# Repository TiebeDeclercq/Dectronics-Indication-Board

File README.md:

# DECTRONICS INDICATION BOARD

The LED PCB is a versatile lighting interface board designed to connect standard LEDs and addressable WS2812B RGB LEDs to systems via FCP connectors or pin headers. It provides flexible soldering options to choose which connection option you want to use.
## Overview

This PCB serves as a lighting expansion board that can be integrated with various systems through standardized connectors. It features both power indicator LEDs and a chain of WS2812B addressable RGB LEDs, making it suitable for status indication, ambient lighting, and visual feedback in electronic projects.

## Features

- **Power/Status LEDs**: 4 individual LEDs with current-limiting resistors
- **WS2812B Support**: Chain of 6 addressable RGB LEDs
- **Dual FCP Connectors**: Front and back connection options
- **Header Connectors**: Standard 2.54mm pin headers for breadboard compatibility
- **Flexible Soldering**: Multiple connection points for different configurations
- **Mounting Holes**: Two mounting holes for secure installation
## Hardware Schematic

## Assembled PCB

## Connector Pinout
### FCP Connector (J2/J4)

| Pin | Function |
| --- | -------- |
| 1   | LED1/VCC |
| 2   | LED2     |
| 3   | LED3     |
| 4   | LED4     |
| 5   | LED5/RX  |
| 6   | LED6/TX  |
| 7   | GND      |

### Header Connector (J1)

|Pin|Function|
|---|---|
|1|LED1/VCC|
|2|LED2|
|3|LED3|
|4|LED4|
|5|LED5/RX|
|6|LED6/TX|
|7|GND|

## Soldering Options

The PCB includes multiple solder jumpers (JP1-JP4) that allow you to configure the connections based on your specific requirements:

- **JP1/JP3**: Via these jumpers you can configure if you want to use it as an adressable led or to see the rx progress on the led
- **JP2/JP4**: Via these jumpers you can configure if you want to use it as an adressable led or to see the tx progress on the led

### Soldering Configurations:

You can choose to solder different components depending on your needs:

1. **Status LEDS**: Solder R3-R6 and D1-D4 for basic power/status indication
2. **RGB LEDS**: Solder the WS2812B LEDs (D7-D12) and appropriate jumpers
## Mounting

The PCB includes two mounting holes (H1 and H2) for secure installation using M3 screws.

## Usage Examples

### Status Indication

Use the individual LEDs (D1-D4) to indicate system status, power levels, or operational modes.

### Ambient Lighting

Program the WS2812B LEDs for decorative lighting effects, color-coded status information, or animations.

### Visual Feedback

Create visual feedback systems using the addressable RGB LEDs to indicate process states, alert conditions, or data visualization.
## Compatibility

This LED PCB is designed to work with:

- Systems using FCP connector standard
- Breadboard-compatible systems via pin headers
- Any microcontroller capable of driving WS2812B LEDs

© DECTRONICS

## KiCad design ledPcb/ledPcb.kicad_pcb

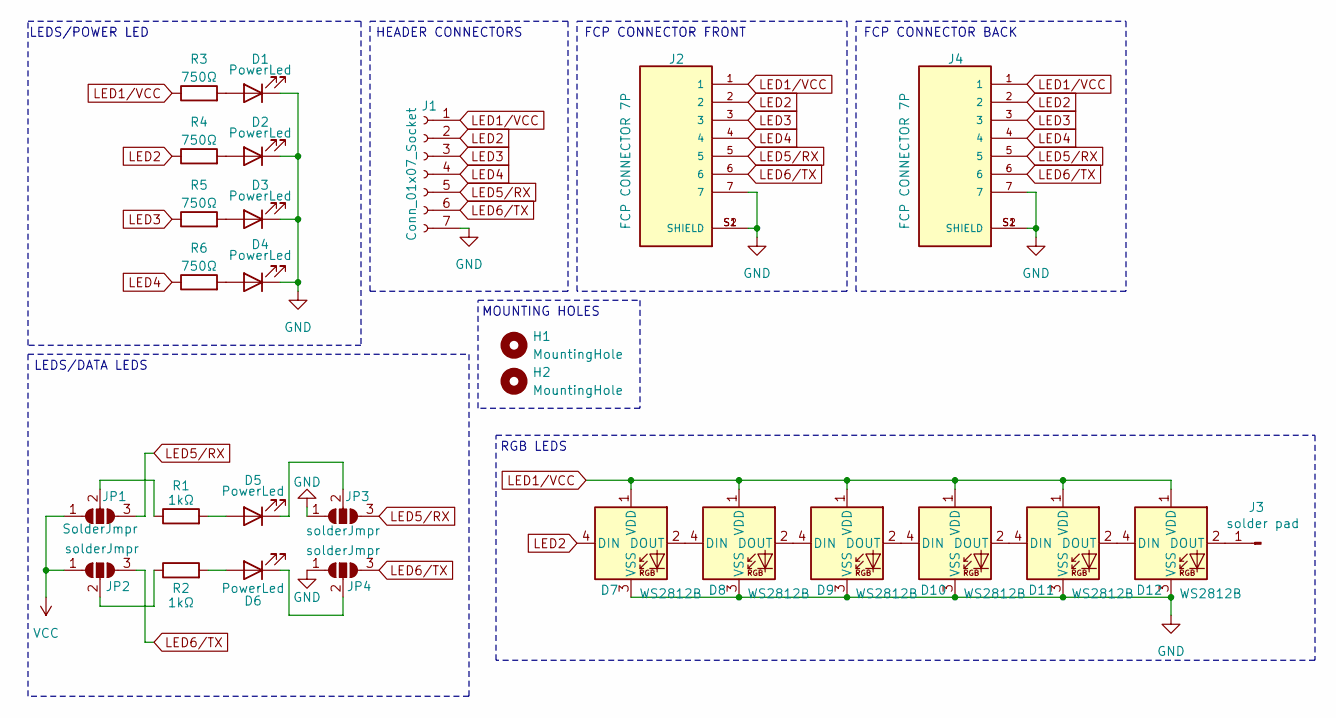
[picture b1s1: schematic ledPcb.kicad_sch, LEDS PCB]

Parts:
D1, D2, D3, D4, D5, D6: PowerLed; LED_0805_2012Metric
D7, D8, D9, D10, D11, D12: WS2812B; LED_WS2812B_PLCC4_5.0x5.0mm_P3.2mm
H1, H2: MountingHole; MountingHole_2.2mm_M2
J1: Conn_01x07_Socket; PinHeader_1x07_P2.54mm_Vertical
J2, J4: FCP CONNECTOR 7P; FCP7P; PARTREV A4
J3: solder pad; TestPoint_Pad_D1.5mm
JP1: SolderJmpr; SolderJumper-3_P2.0mm_Open_TrianglePad1.0x1.5mm_NumberLabels
JP2, JP3, JP4: solderJmpr; SolderJumper-3_P2.0mm_Open_TrianglePad1.0x1.5mm_NumberLabels
R1, R2: 1kΩ; R_0805_2012Metric_Pad1.20x1.40mm_HandSolder
R3, R4, R5, R6: 750Ω; R_0805_2012Metric_Pad1.20x1.40mm_HandSolder

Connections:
GND: D1.1 (K), D2.1 (K), D3.1 (K), D4.1 (K), D7.3 (VSS), D8.3 (VSS), D9.3 (VSS), D10.3 (VSS), D11.3 (VSS), D12.3 (VSS), J1.7, J2.7, J2.S1 (SHIELD), J2.S2 (SHIELD), J4.7, J4.S1 (SHIELD), J4.S2 (SHIELD), JP3.1 (A), JP4.1 (A)
LED1/VCC: D7.1 (VDD), D8.1 (VDD), D9.1 (VDD), D10.1 (VDD), D11.1 (VDD), D12.1 (VDD), J1.1, J2.1, J4.1, R3.1
LED2: D7.4 (DIN), J1.2, J2.2, J4.2, R4.1
LED3: J1.3, J2.3, J4.3, R5.1
LED4: J1.4, J2.4, J4.4, R6.1
LED5/RX: J1.5, J2.5, J4.5, JP1.3 (B), JP3.3 (B)
LED6/TX: J1.6, J2.6, J4.6, JP2.3 (B), JP4.3 (B)
unnamed: D1.2 (A), R3.2
unnamed: D2.2 (A), R4.2
unnamed: D3.2 (A), R5.2
unnamed: D4.2 (A), R6.2
unnamed: D5.2 (A), R1.2
unnamed: D5.1 (K), JP3.2 (C)
unnamed: D6.2 (A), R2.2
unnamed: D6.1 (K), JP4.2 (C)
unnamed: D7.2 (DOUT), D8.4 (DIN)
unnamed: D8.2 (DOUT), D9.4 (DIN)
unnamed: D9.2 (DOUT), D10.4 (DIN)
unnamed: D10.2 (DOUT), D11.4 (DIN)
unnamed: D11.2 (DOUT), D12.4 (DIN)
unnamed: D12.2 (DOUT), J3.1
unnamed: JP1.2 (C), R1.1
unnamed: JP2.2 (C), R2.1
VCC: JP1.1 (A), JP2.1 (A)

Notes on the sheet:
LEDS/POWER LED
LEDS/DATA LEDS
RGB LEDS
FCP CONNECTOR BACK
MOUNTING HOLES
FCP CONNECTOR FRONT
HEADER CONNECTORS

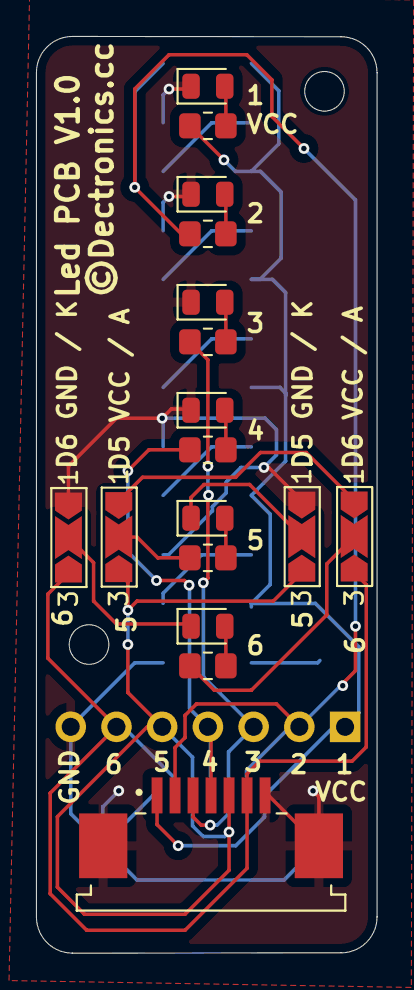
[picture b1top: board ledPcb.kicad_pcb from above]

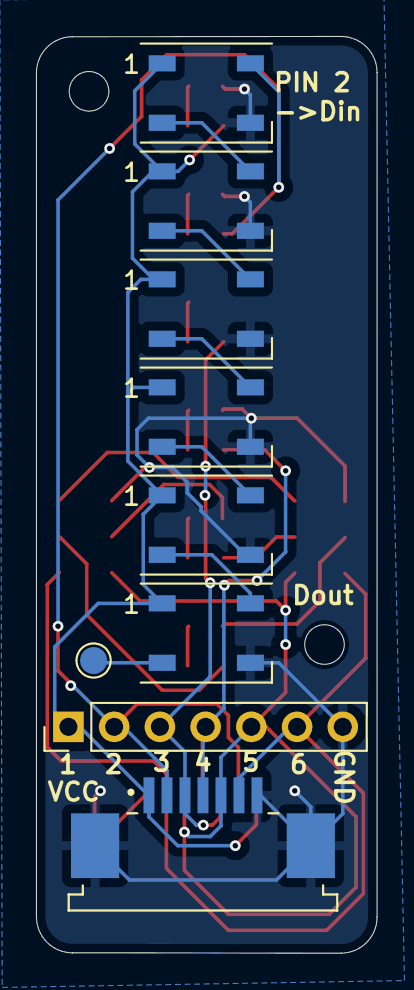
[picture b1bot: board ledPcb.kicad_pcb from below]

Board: 2 copper layers, 18.9 x 50.9 mm, 28 parts (9 on the bottom side), 24 nets.

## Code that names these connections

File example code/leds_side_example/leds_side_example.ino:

// Pin definitions for LED control
#define LED1_PIN        2    // LED1
#define LED2_PIN        0    // LED2
#define LED3_PIN        4    // LED3

// Optional, only if you have configured the correct solder pads
#define LED4_PIN     16    // LED5/RX data indicator
#define LED5_PIN     17    // LED6/TX data indicator

void setup() {
  pinMode(LED1_PIN, OUTPUT);
  pinMode(LED2_PIN, OUTPUT);
  pinMode(LED3_PIN, OUTPUT);

  pinMode(LED4_PIN, OUTPUT);
  pinMode(LED5_PIN, OUTPUT);
}

void loop() {
  digitalWrite(LED1_PIN, HIGH);
  digitalWrite(LED3_PIN, LOW);
  delay(200);
  digitalWrite(LED1_PIN, LOW);
  digitalWrite(LED2_PIN, HIGH);
  delay(200);
  digitalWrite(LED2_PIN, LOW);
  digitalWrite(LED3_PIN, HIGH);
  delay(200);
}

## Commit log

2025-04-06 board
2025-04-12 ready for public

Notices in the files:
ledPcb/ledPcb.kicad_pcb:
©Dectronics.cc
